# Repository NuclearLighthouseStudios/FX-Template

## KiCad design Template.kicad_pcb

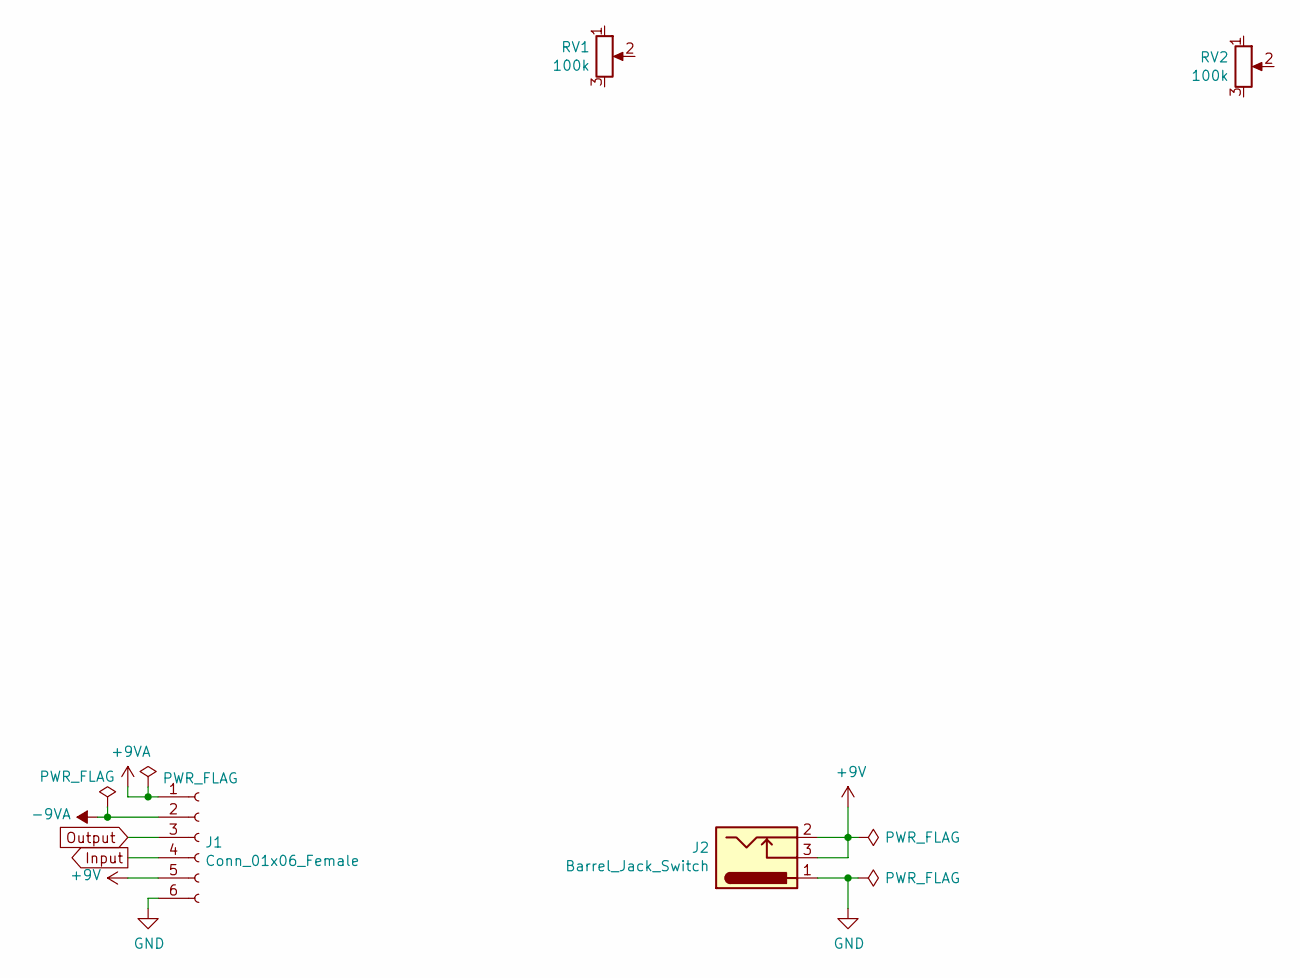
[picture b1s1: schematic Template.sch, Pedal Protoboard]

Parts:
J1: Conn_01x06_Female; PinHeader_1x06_P2.54mm_Vertical
J2: Barrel_Jack_Switch; BarrelJack_Horizontal_Short
RV1, RV2: 100k; Potentiometer_Alps_RK09K_Single_Vertical

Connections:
+9V: J1.5, J2.2, J2.3
+9VA: J1.1
-9VA: J1.2
GND: J1.6, J2.1
Input: J1.4
Output: J1.3

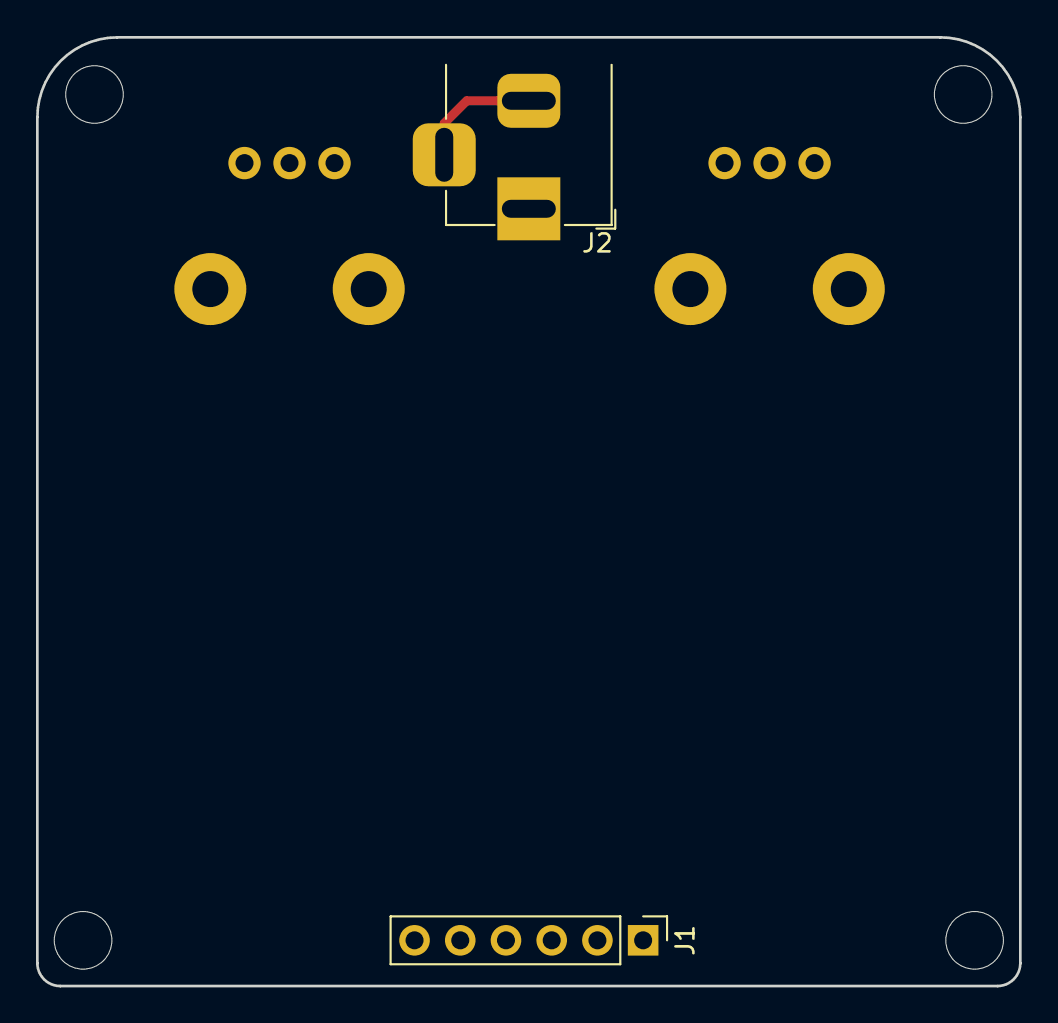
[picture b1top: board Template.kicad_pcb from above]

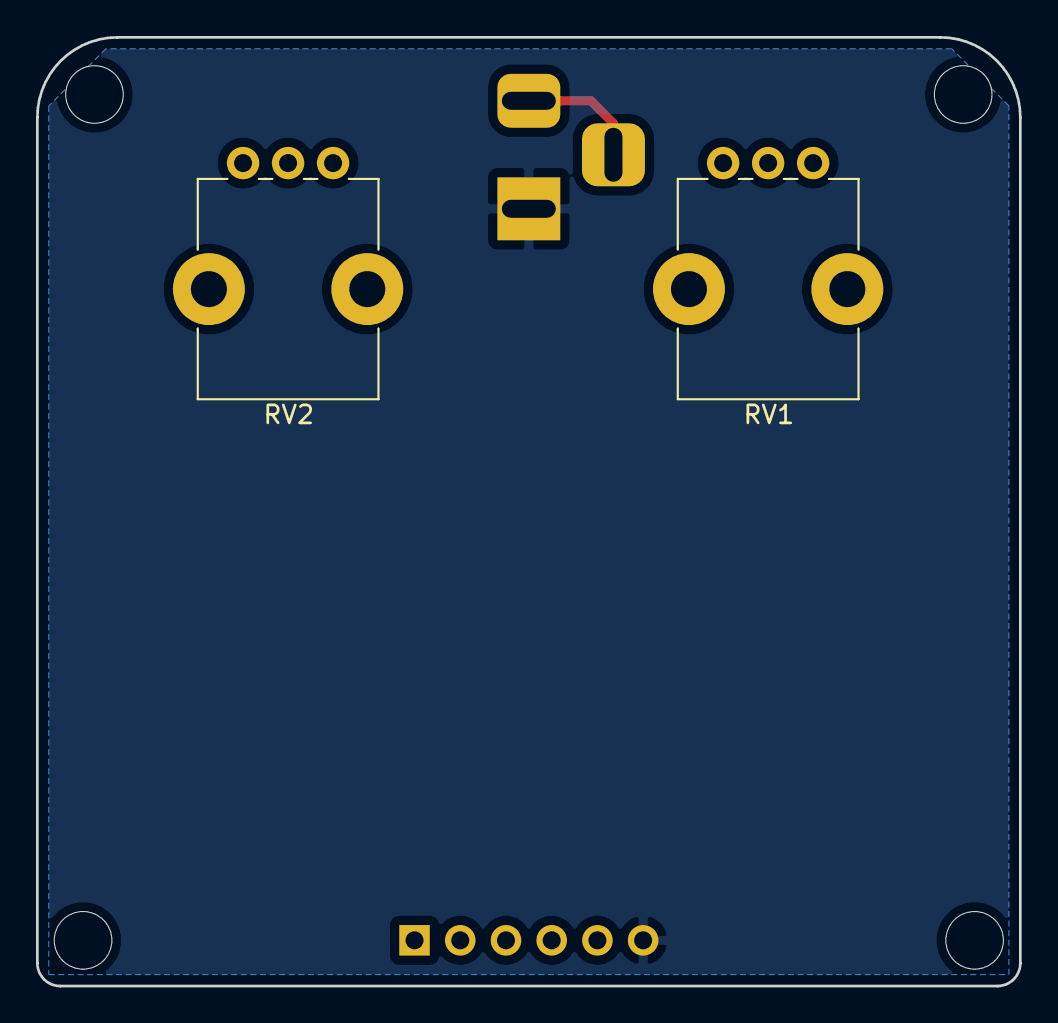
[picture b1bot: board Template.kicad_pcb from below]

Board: 2 copper layers, 54.6 x 52.7 mm, 4 parts (2 on the bottom side), 2 nets.

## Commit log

2020-03-11 Initial Commit! Yay!

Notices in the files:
Template.kicad_pcb:
CC BY-SA
